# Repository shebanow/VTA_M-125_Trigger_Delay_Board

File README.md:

# VTA_M-125_Trigger_Delay_Board

The VTA M-125 amp is a great, 125w tube-based audio amplifier (monoblock). Available in kit form or preassembled from 
http://www.tubes4hifi.com/bob.htm#M125. 

One thing lacking in the amp is a 12v audio trigger capability. So, I modified the amp design to include a trigger board that can also function as a power delay for the plate power (main power in the amp). This is similar to the "Time Delay Relay" board sold on Tubes4HiFi.com except it also adds 12v trigger capability.

Available in this reposistory are:
* Gerber files for a PCB 
* PDFs for the schematic and chassis layout
* Autodesk Eagle project files
* Complete BOM (bill of materials) (I used Digikey to purchase parts)
* Instructions (below) on how to install it.

# Installation instructions

To install this board, follow these directions:
1. Order PCBs using the Gerber files included in this repository. This design uses 2-layer PCBs and includes a part layout silkscreen.
2. Order parts using the BOM from your favorite parts distributor. 
3. Machine the chassis using the PDF drawing included in this repository. 
4. Once you have both PCBs and parts, assemble the trigger/delay board. I used small solder lugs to attach wires to my board, but in theory, you could dispense with that and solder wires directly to the through holes (though w/ 14 gauge wires, could be a trick).
5. Install the 3.5mm trigger connector in the chassis between the RCA input jack and the speaker lugs.
6. Install the trigger/delay board in the chassis using small M3 screws and standoffs. Attach the boards using M3 washers and lock nuts
    * For the standoffs, I used https://www.digikey.com/product-detail/en/raf-electronic-hardware/M2141-3005-SS/1772-2025-ND/7681436
    * For the M3 screws, you could use https://www.digikey.com/product-detail/en/w-rth-elektronik/97790403211/732-13707-ND/10056390 (nylon) or in my case, https://www.amazon.com/gp/product/B00F31QQYU/ref=ppx_yo_dt_b_asin_title_o07_s00?ie=UTF8&psc=1 (black).
7. Prior to starting the WIRING instructions on page 5 of the assembly instructions, perform these steps:
    * Twist a pair of 24" long red and black, 14-gauge stranded hookup wires. On one end of the pair, leave roughly 3" untwisted, and on the other end, 4" untwisted. Strip the 3" end of each wire 1/2". Strip the red wire of the 4" end 1/2" as well, but only strip the black end 3/8". 
    * Cut a 8" long red, 14-gauge stranded hookup wire. Strip 1/2" on one end and 3/8" on the other. 
    * Separate the wires in the 4" end of the first twisted pair. Twist the 8" wire with the red wire of the first twisted pair, end-to-end. At the junction of the red and black wires of the longer twisted pair, now twist the remainder of the 8" red wire with the black wire of the longer twisted pair. At the completion of this step, the red and black wires should line up.
    * Starting with the 3" end, attach the twisted pair assembly along the inside chassis from the fuse folder (black wire end), behind the power transformer, along the left edge (see machining diagram for definition of "left"), to the left of the tube sockets, then along the front to the power switch. You can use wire ties to hold the cable to the chassis if necessary.
    * Solder the black wire on the 3" end to the outer lug of the fuse holder. Solder the red wire of the same end to the "left upper" lug of the IEC power connector. Use a small 3" (or so) 14 gauge wire to connect the other upper lug of the IEC connector to the outside lug of the fuse holder. Follow the instructions in the manual for connecting the chassis lug (ground) of the IEC connector.
    * On the 4" end of the twisted pair assembly, solder one red wire to the lower lug of the power switch and one red wire to the other lug; the order doesn't matter. Solder the black wire to the "AC_COMM" lug of the trigger/delay board. Solder the other end of the 8" wire to the "AC_LINE" lug of the trigger/delay board.
8. Connect the trigger.
    * Twist a set of three 14" 22-gauge hookup wires. Preferrably, green, black, and red, but if only one color is available, be sure to mark the wires on each end so you know which wire is which. Strip one end to 3/8" and the other to 1/2". 
    * Extend the twisted set between the trigger/delay board "TRIG_xxx" pins and the 3.5mm trigger jack, running the cable along the back-inside of the chassis past the fuse holder and IEC power conector, then up along side the right side of the power transformer and on to the trigger board. 
    * Starting with 
9. At this point, the trigger/delay board is testable. 
    * Plug in an **UNCONNECTED** 12v trigger cable into the trigger jack on the rear panel. Plug in the power cable to the chassis, being **VERY CAREFUL** about high voltage now in the chassis. With the power switch on, you should see the LED light on the trigger/delay board light up red. You should also be able to measure roughly 12v DC between the "TRIG_RING" and "TRIG_GND lugs on the trigger/delay board. If the light does not light up, check the fuse, then check the board for shorts, then each part of proper insertion - standard board debugging. 
    * Unplug the trigger cable from the trigger jack. You should see the LED light blue, then after a delay, light to green. Adjust the potentiometer on the trigger delay board to get the desired turn on-delay (time in blue state). The delay should be adjustable from short (~1 sec) to long (~27 sec). You can test this by turning the amp on and off with the main power switch. During the delay period, the LED will light blue. If a solid state rectifier is used, a 17 sec delay is recommended. If a tube rectifier is use, a short delay (1 sec) is ok, but you cna set this as desired. As designed, it is not possible to have no delay. 
    * If all is well, unplug power.
10. Instead of hooking up the red power transformer wires as stated in step 2 of the WIRING instructions on page 5, do the following:
    * Twist the pair of RED leads from the power transformer together and extend to the "TRANS_RED1" and "TRANS_RED2" lugs of the trigger/delay board. Shorten as needed, stripping 3/8" from each end. Solder to the "TRANS_RED1" and "TRANS_RED2" lugs (doesn't matter which wire goes to which). 
    * Twist a pair of RED, 22 gauge hookup wires, length as needed, to connect the "V5_PIN4" and "V5_PIN6" lugs on the trigger/delay board to the #4 and #6 lugs of the V5 tube. Strip one end of the pair to 3/8" and the other to 1/2". Solder the 3/8" end to the "V5_PIN4" and "V5_PIN6" lugs on the trigger/delay board and the other 1/2" end to the 4 and #6 lugs of the V5 tube. Wire order does not matter.

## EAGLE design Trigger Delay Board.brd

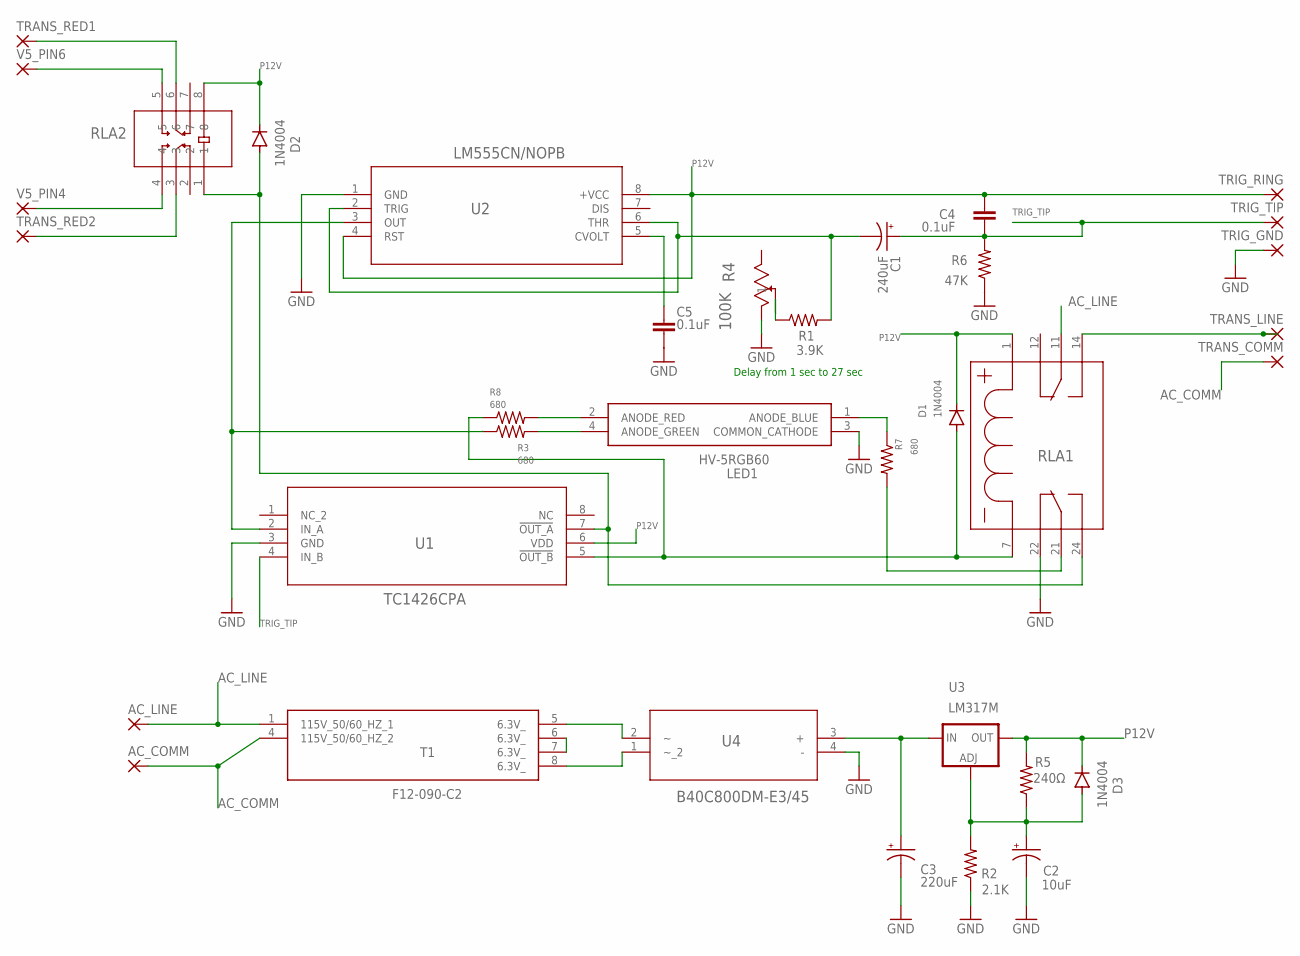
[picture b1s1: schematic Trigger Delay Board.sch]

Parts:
AC_COMM: 3,81/1,4
AC_LINE: 3,81/1,4
C1: 240uF; E1,8-4
C2: 10uF; E1,8-4
C3: 220uF; E1,8-4
C4, C5: 0.1uF; C025-024X044
D1, D2, D3: 1N4004; DO41-10
LED1: HV-5RGB60; HV5RGB25
R1: 3.9K; 0207/10
R2: 2.1K; 0207/10
R3, R7, R8: 680; 0207/10
R4: 100K; RES3_64W
R5: 240Ω; 0207/10
R6: 47K; 0207/10
RLA1: RTE24012; RELAY-DPDT_5MM
RLA2: G2RL-2_DC12; RELAY_G2RL-2
T1: F12-090-C2; F12090C2
TRANS_COMM: 3,81/1,4
TRANS_LINE: 3,81/1,4
TRANS_RED1, TRANS_RED2: 3,81/1,4
TRIG_GND: 3,81/1,4
TRIG_RING: 3,81/1,4
TRIG_TIP: 3,81/1,4
U1: TC1426CPA; PDIP8_300MC
U2: LM555CN/NOPB; N08E
U3: LM317MB; TO220L1; PARTNUMBER LM317M
U4: B40C800DM-E3/45; DIP4_DFM
V5_PIN4, V5_PIN6: 3,81/1,4

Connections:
AC_COMM: AC_COMM.1, T1.4 (115V_50/60_HZ_2), TRANS_COMM.1
AC_LINE: AC_LINE.1, RLA1.11 (3), T1.1 (115V_50/60_HZ_1)
GND: C2.-, C3.-, C5.2, LED1.3 (COMMON_CATHODE), R2.1, R4.1, R6.1, RLA1.22 (7), TRIG_GND.1, U1.3 (GND), U2.1 (GND), U4.4 (-)
unnamed: C2.+, D3.A, R2.2, R5.1, U3.1 (ADJ)
unnamed: T1.6 (6.3V_), T1.7 (6.3V_)
unnamed: T1.5 (6.3V_), U4.2
unnamed: T1.8 (6.3V_), U4.1 (~_2)
unnamed: D2.A, RLA1.24 (5), RLA2.1, U1.7 (!OUT_A)
unnamed: R3.1, U1.2 (IN_A), U2.3 (OUT)
unnamed: LED1.2 (ANODE_RED), R8.2
unnamed: R1.1, R4.2
unnamed: C5.1, U2.5 (CVOLT)
unnamed: D1.A, R8.1, RLA1.7 (8), U1.5 (!OUT_B)
unnamed: R7.2, RLA1.21 (6)
unnamed: C1.-, R1.2, U2.2 (TRIG), U2.6 (THR)
unnamed: LED1.1 (ANODE_BLUE), R7.1
unnamed: LED1.4 (ANODE_GREEN), R3.2
unnamed: C3.+, U3.3 (IN), U4.3 (+)
P12V: C4.1, D1.C, D2.C, D3.C, R5.2, RLA1.1, RLA2.8, TRIG_RING.1, U1.6 (VDD), U2.4 (RST), U2.8 (+VCC), U3.2 (OUT)
TRANS_LINE: RLA1.14 (4), TRANS_LINE.1
TRANS_RED1: RLA2.6, TRANS_RED1.1
TRANS_RED2: RLA2.3, TRANS_RED2.1
TRIG_TIP: C1.+, C4.2, R6.2, TRIG_TIP.1, U1.4 (IN_B)
V5_PIN4: RLA2.4, V5_PIN4.1
V5_PIN6: RLA2.5, V5_PIN6.1

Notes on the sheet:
Delay from 1 sec to 27 sec

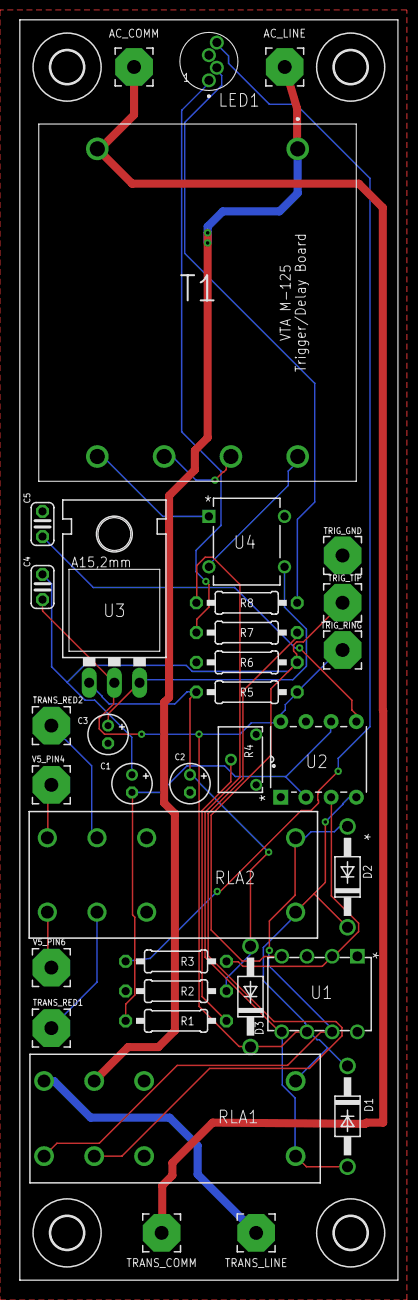
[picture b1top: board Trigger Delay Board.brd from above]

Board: 2 copper layers, 38.1 x 127.0 mm, 39 parts (0 on the bottom side), 25 nets.

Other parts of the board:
U$1, U$2, U$7, U$8: 3,3

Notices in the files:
parts and their libraries:
COPYRIGHT: Copyright (C) 2016 Accelerated Designs. All rights reserved
COPYRIGHT: Copyright (C) 2018 Accelerated Designs. All rights reserved
